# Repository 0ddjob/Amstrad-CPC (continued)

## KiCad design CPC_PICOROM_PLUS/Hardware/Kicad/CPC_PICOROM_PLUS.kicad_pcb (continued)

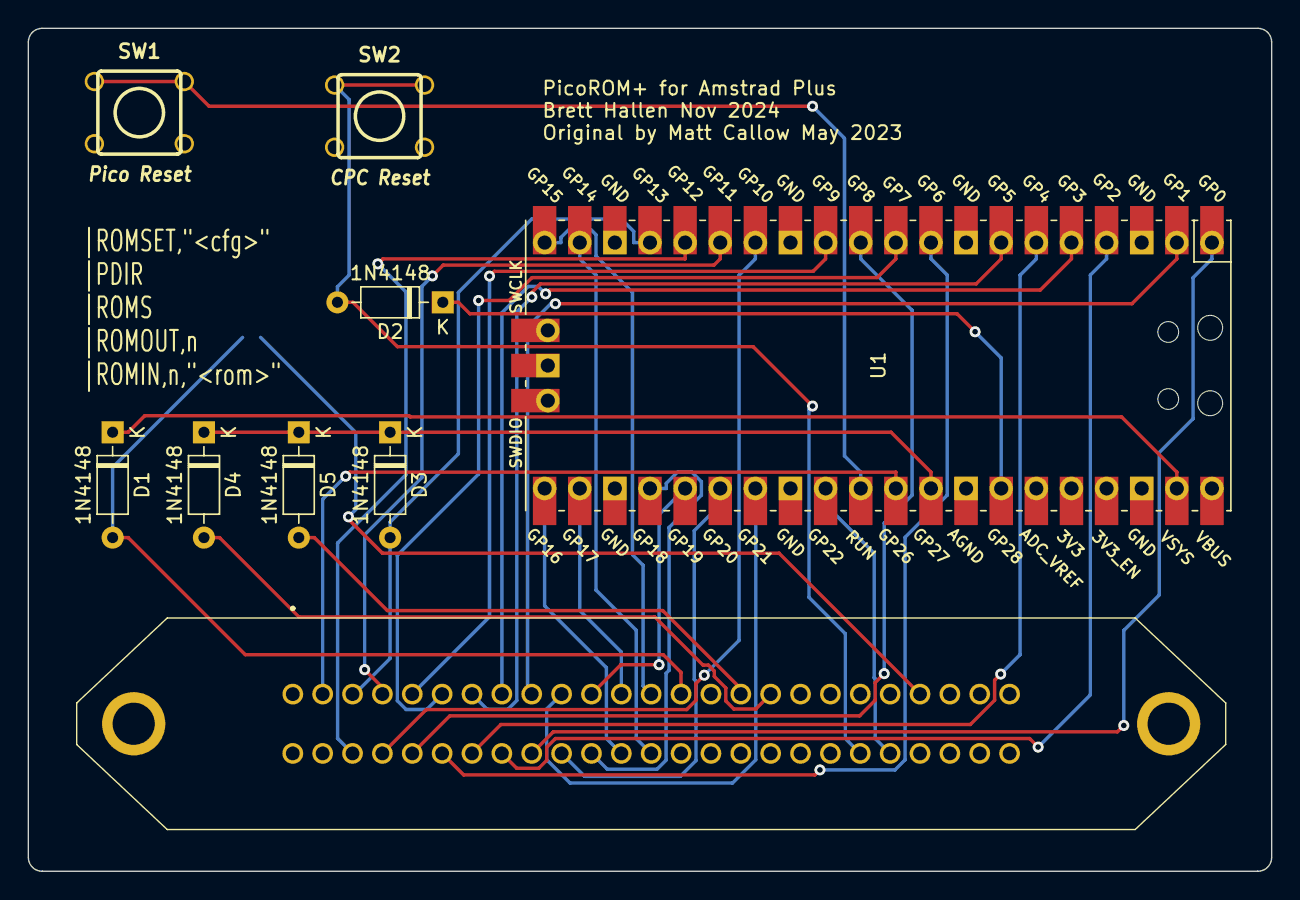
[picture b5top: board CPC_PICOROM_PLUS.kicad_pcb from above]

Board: 2 copper layers, 89.9 x 61.0 mm, 10 parts (1 on the bottom side), 34 nets.

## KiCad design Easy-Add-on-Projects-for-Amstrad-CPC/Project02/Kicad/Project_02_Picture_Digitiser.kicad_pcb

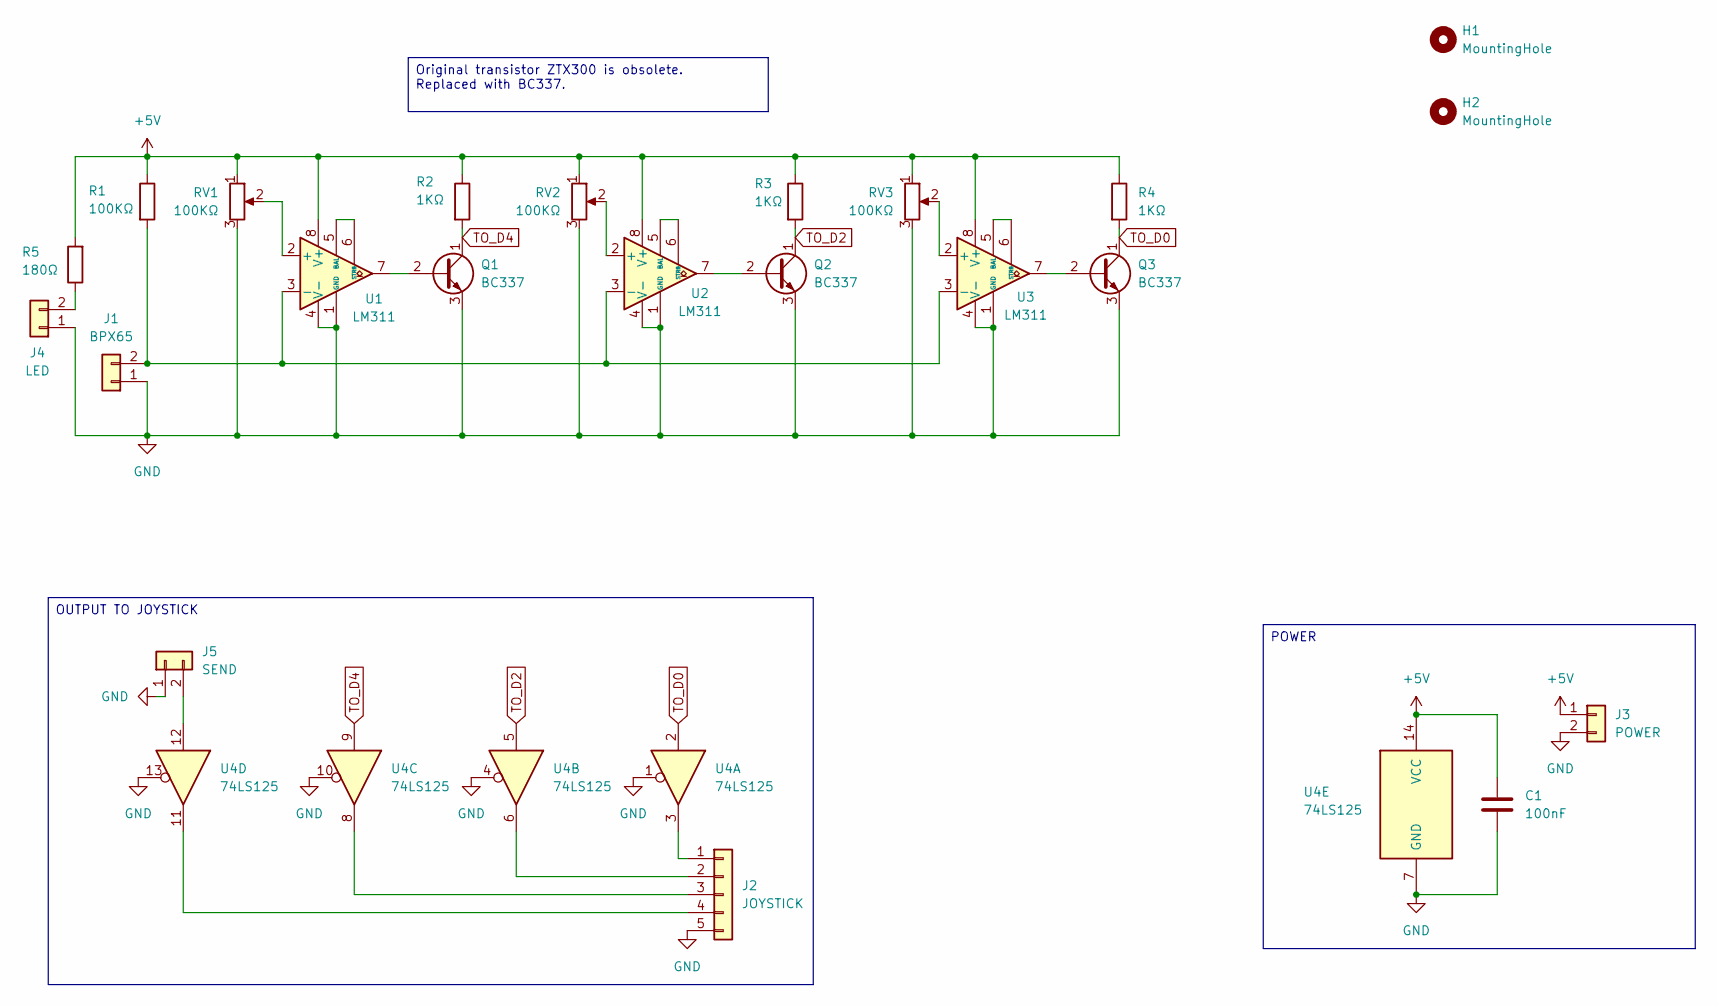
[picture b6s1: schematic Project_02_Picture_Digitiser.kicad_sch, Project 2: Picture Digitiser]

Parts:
C1: 100nF; C_Disc_D3.4mm_W2.1mm_P2.50mm
H1, H2: MountingHole; MountingHole_3.2mm_M3
J1: BPX65; PinSocket_1x02_P2.54mm_Vertical
J2: JOYSTICK; PinSocket_1x05_P2.54mm_Vertical
J3: POWER; PinSocket_1x02_P2.54mm_Vertical
J4: LED; PinSocket_1x02_P2.54mm_Vertical
J5: SEND; PinSocket_1x02_P2.54mm_Vertical
Q1, Q2, Q3: BC337; TO-92_Inline
R1: 100KΩ; R_Axial_DIN0207_L6.3mm_D2.5mm_P7.62mm_Horizontal
R2, R3, R4: 1KΩ; R_Axial_DIN0207_L6.3mm_D2.5mm_P7.62mm_Horizontal
R5: 180Ω; R_Axial_DIN0207_L6.3mm_D2.5mm_P7.62mm_Horizontal
RV1, RV2, RV3: 100KΩ; Potentiometer_Bourns_3296W_Vertical
U1, U2, U3: LM311; DIP-8_W7.62mm
U4: 74LS125; DIP-14_W7.62mm

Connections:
+5V: C1.1, J3.1, R1.1, R2.1, R3.1, R4.1, R5.2, RV1.1, RV2.1, RV3.1, U1.8 (V+), U2.8 (V+), U3.8 (V+), U4.14 (VCC)
GND: C1.2, J1.1, J2.5, J3.2, J4.1, J5.1, Q1.3 (E), Q2.3 (E), Q3.3 (E), RV1.3, RV2.3, RV3.3, U1.1 (GND), U1.4 (V-), U2.1 (GND), U2.4 (V-), U3.1 (GND), U3.4 (V-), U4.1, U4.4, U4.7 (GND), U4.10, U4.13
unnamed: J1.2, R1.2, U1.3 (-), U2.3 (-), U3.3 (-)
unnamed: J2.1, U4.3
unnamed: J2.2, U4.6
unnamed: J2.3, U4.8
unnamed: J2.4, U4.11
unnamed: J4.2, R5.1
unnamed: J5.2, U4.12
unnamed: Q1.2 (B), U1.7
unnamed: Q2.2 (B), U2.7
unnamed: Q3.2 (B), U3.7
unnamed: RV1.2, U1.2 (+)
unnamed: U1.5 (BAL), U1.6 (STRB)
unnamed: RV2.2, U2.2 (+)
unnamed: U2.5 (BAL), U2.6 (STRB)
unnamed: RV3.2, U3.2 (+)
unnamed: U3.5 (BAL), U3.6 (STRB)
TO_D0: Q3.1 (C), R4.2, U4.2
TO_D2: Q2.1 (C), R3.2, U4.5
TO_D4: Q1.1 (C), R2.2, U4.9

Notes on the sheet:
POWER
OUTPUT TO JOYSTICK
Original transistor ZTX300 is obsolete. Replaced with BC337.

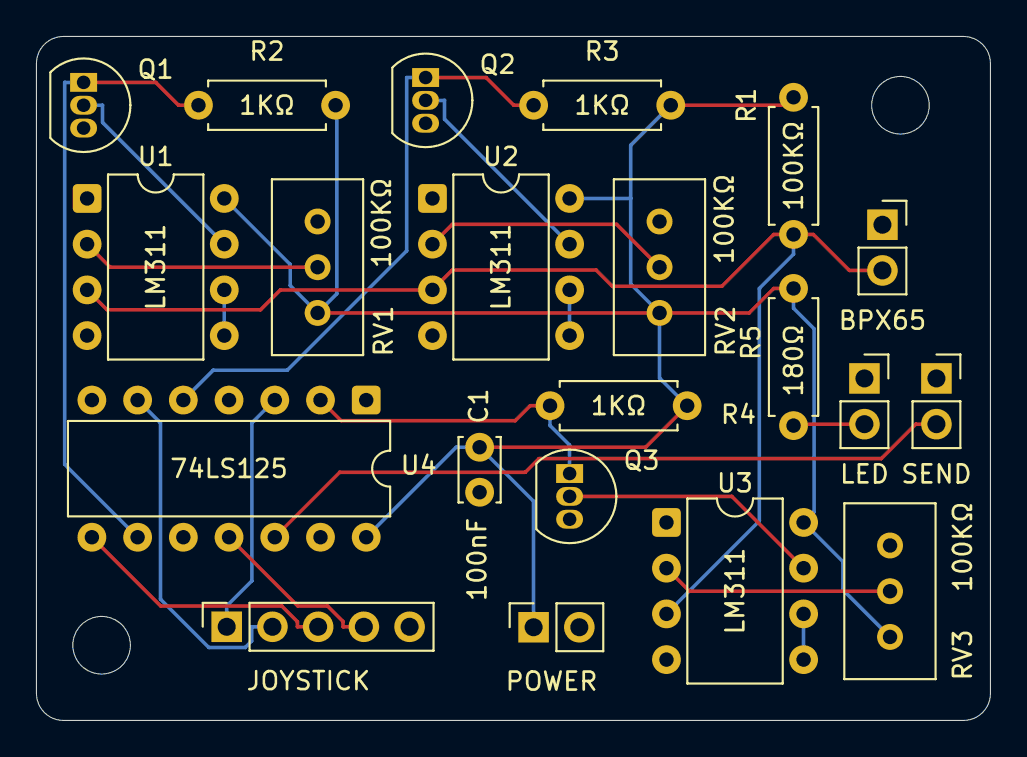
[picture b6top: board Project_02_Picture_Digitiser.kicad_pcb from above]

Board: 2 copper layers, 53.0 x 38.0 mm, 23 parts (0 on the bottom side), 21 nets.

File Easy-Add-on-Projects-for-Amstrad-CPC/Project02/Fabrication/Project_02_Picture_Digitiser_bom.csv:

Designator,Quantity,Value,Footprint,Package,MPN,DNP,Mount_Type,Description,Sim.Device,Sim.Type,Sim.Pins
C1,1,100nF,C_Disc_D3.4mm_W2.1mm_P2.50mm,,,,tht,Unpolarized capacitor,,,
J1,1,BPX65,PinSocket_1x02_P2.54mm_Vertical,,,,tht,"Generic connector, single row, 01x02, script generated (kicad-library-utils/schlib/autogen/connector/)",,,
J2,1,JOYSTICK,PinSocket_1x05_P2.54mm_Vertical,,,,tht,"Generic connector, single row, 01x05, script generated (kicad-library-utils/schlib/autogen/connector/)",,,
J3,1,POWER,PinSocket_1x02_P2.54mm_Vertical,,,,tht,"Generic connector, single row, 01x02, script generated (kicad-library-utils/schlib/autogen/connector/)",,,
J4,1,LED,PinSocket_1x02_P2.54mm_Vertical,,,,tht,"Generic connector, single row, 01x02, script generated (kicad-library-utils/schlib/autogen/connector/)",,,
J5,1,SEND,PinSocket_1x02_P2.54mm_Vertical,,,,tht,"Generic connector, single row, 01x02, script generated (kicad-library-utils/schlib/autogen/connector/)",,,
"Q1, Q2, Q3",3,ZTX300,TO-92_Inline,,,,tht,"Bipolar transistor symbol for simulation only, substrate tied to the emitter",NPN,GUMMELPOON,1=C 2=B 3=E
R1,1,100KΩ,R_Axial_DIN0207_L6.3mm_D2.5mm_P7.62mm_Horizontal,,,,tht,Resistor,,,
"R2, R3, R4",3,1KΩ,R_Axial_DIN0207_L6.3mm_D2.5mm_P7.62mm_Horizontal,,,,tht,Resistor,,,
R5,1,180Ω,R_Axial_DIN0207_L6.3mm_D2.5mm_P7.62mm_Horizontal,,,,tht,Resistor,,,
"RV1, RV2, RV3",3,100KΩ,Potentiometer_Bourns_3296W_Vertical,,,,tht,Potentiometer,,,
"U1, U2, U3",3,LM311,DIP-8_W7.62mm,,,,tht,"Voltage Comparator, DIP-8/SOIC-8",,,
U4,1,74LS125,DIP-14_W7.62mm,,,,tht,Quad buffer 3-State outputs,,,
